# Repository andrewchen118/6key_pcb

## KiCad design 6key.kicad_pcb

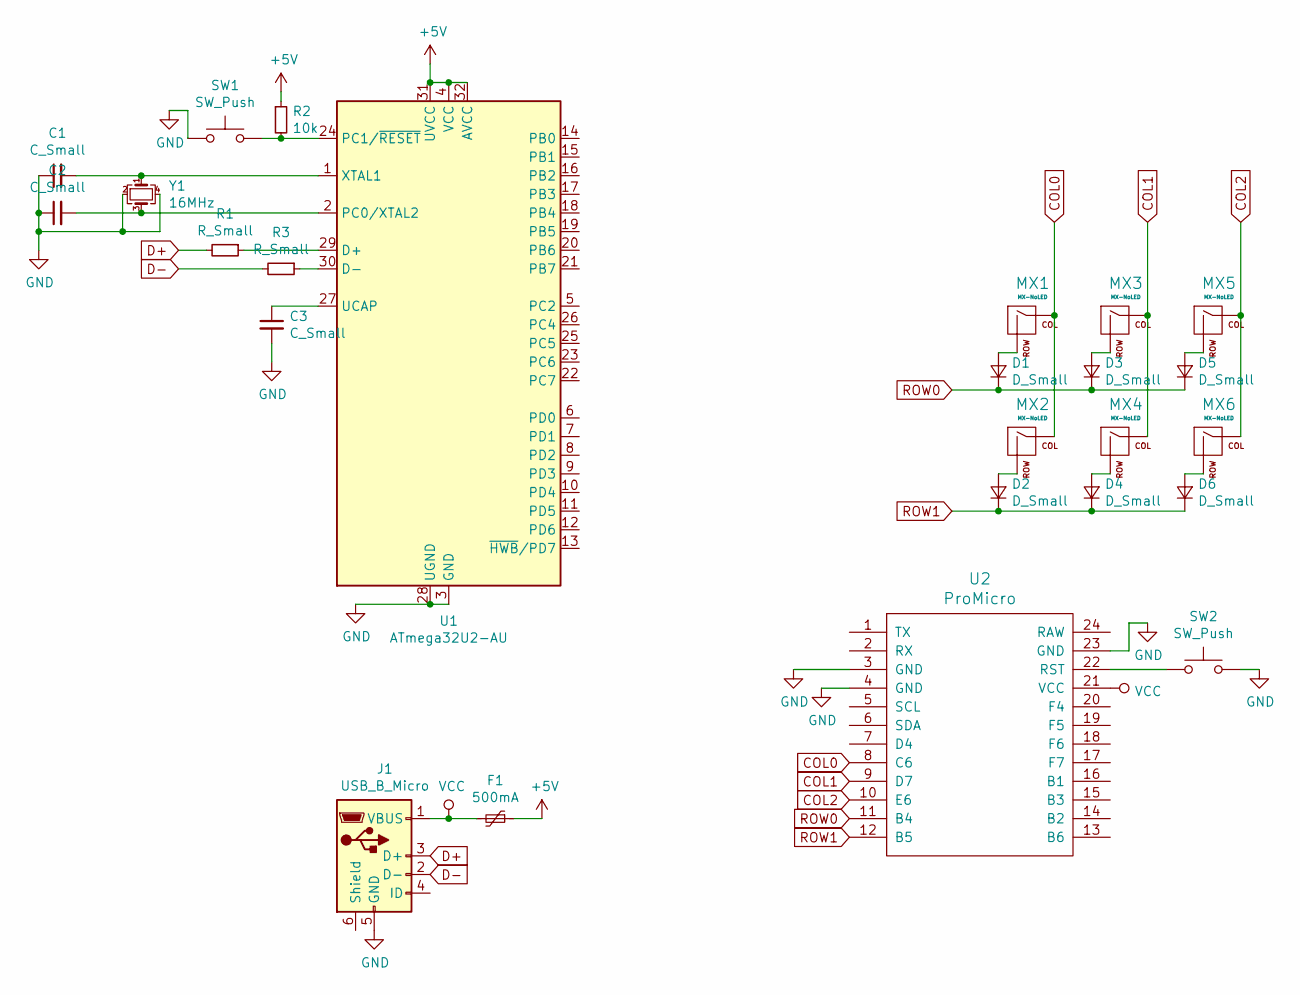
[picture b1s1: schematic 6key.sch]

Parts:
C1, C2, C3: C_Small; C_0805_2012Metric_Pad1.15x1.40mm_HandSolder
D1, D2, D3, D4, D5, D6: D_Small; D_SOD-123
F1: 500mA; Fuse_1206_3216Metric_Pad1.42x1.75mm_HandSolder
J1: USB_B_Micro; Molex-0548190519
MX1, MX2, MX3, MX4, MX5, MX6: MX-NoLED; MXOnly-1U-NoLED
R1: R_Small; R_0815_2038Metric_Pad1.53x4.00mm_HandSolder
R2: 10k; R_0805_2012Metric_Pad1.15x1.40mm_HandSolder
R3: R_Small; R_0805_2012Metric_Pad1.15x1.40mm_HandSolder
SW1, SW2: SW_Push; SKQG-1155865
U1: ATmega32U2-AU; TQFP-32_7x7mm_P0.8mm
U2: ProMicro; ARDUINO_PRO_MICRO
Y1: 16MHz; Crystal_SMD_3225-4Pin_3.2x2.5mm_HandSoldering

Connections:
+5V: F1.1, R2.1, U1.4 (VCC), U1.31 (UVCC), U1.32 (AVCC)
COL0: MX1.1 (COL), MX2.1 (COL), U2.8 (C6)
COL1: MX3.1 (COL), MX4.1 (COL), U2.9 (D7)
COL2: MX5.1 (COL), MX6.1 (COL), U2.10 (E6)
D+: J1.3 (D+), R1.2
D-: J1.2 (D-), R3.2
GND: C1.1, C2.1, C3.2, J1.5 (GND), SW1.1, SW2.2, U1.3 (GND), U1.28 (UGND), U2.3 (GND), U2.4 (GND), U2.23 (GND), Y1.2, Y1.4
unnamed: C1.2, U1.1 (XTAL1), Y1.1
unnamed: C2.2, U1.2 (PC0/XTAL2), Y1.3
unnamed: C3.1, U1.27 (UCAP)
unnamed: D1.2 (A), MX1.2 (ROW)
unnamed: D2.2 (A), MX2.2 (ROW)
unnamed: D3.2 (A), MX3.2 (ROW)
unnamed: D4.2 (A), MX4.2 (ROW)
unnamed: D5.2 (A), MX5.2 (ROW)
unnamed: D6.2 (A), MX6.2 (ROW)
unnamed: R1.1, U1.29 (D+)
unnamed: R2.2, SW1.2, U1.24 (PC1/~RESET)
unnamed: R3.1, U1.30 (D-)
unnamed: SW2.1, U2.22 (RST)
ROW0: D1.1 (K), D3.1 (K), D5.1 (K), U2.11 (B4)
ROW1: D2.1 (K), D4.1 (K), D6.1 (K), U2.12 (B5)
VCC: F1.2, J1.1 (VBUS), U2.21 (VCC)

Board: 2 copper layers, 25 parts (0 on the bottom side), 23 nets, no tracks yet.

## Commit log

2019-08-18 basic schematic
2019-08-18 finished-ish schematic
